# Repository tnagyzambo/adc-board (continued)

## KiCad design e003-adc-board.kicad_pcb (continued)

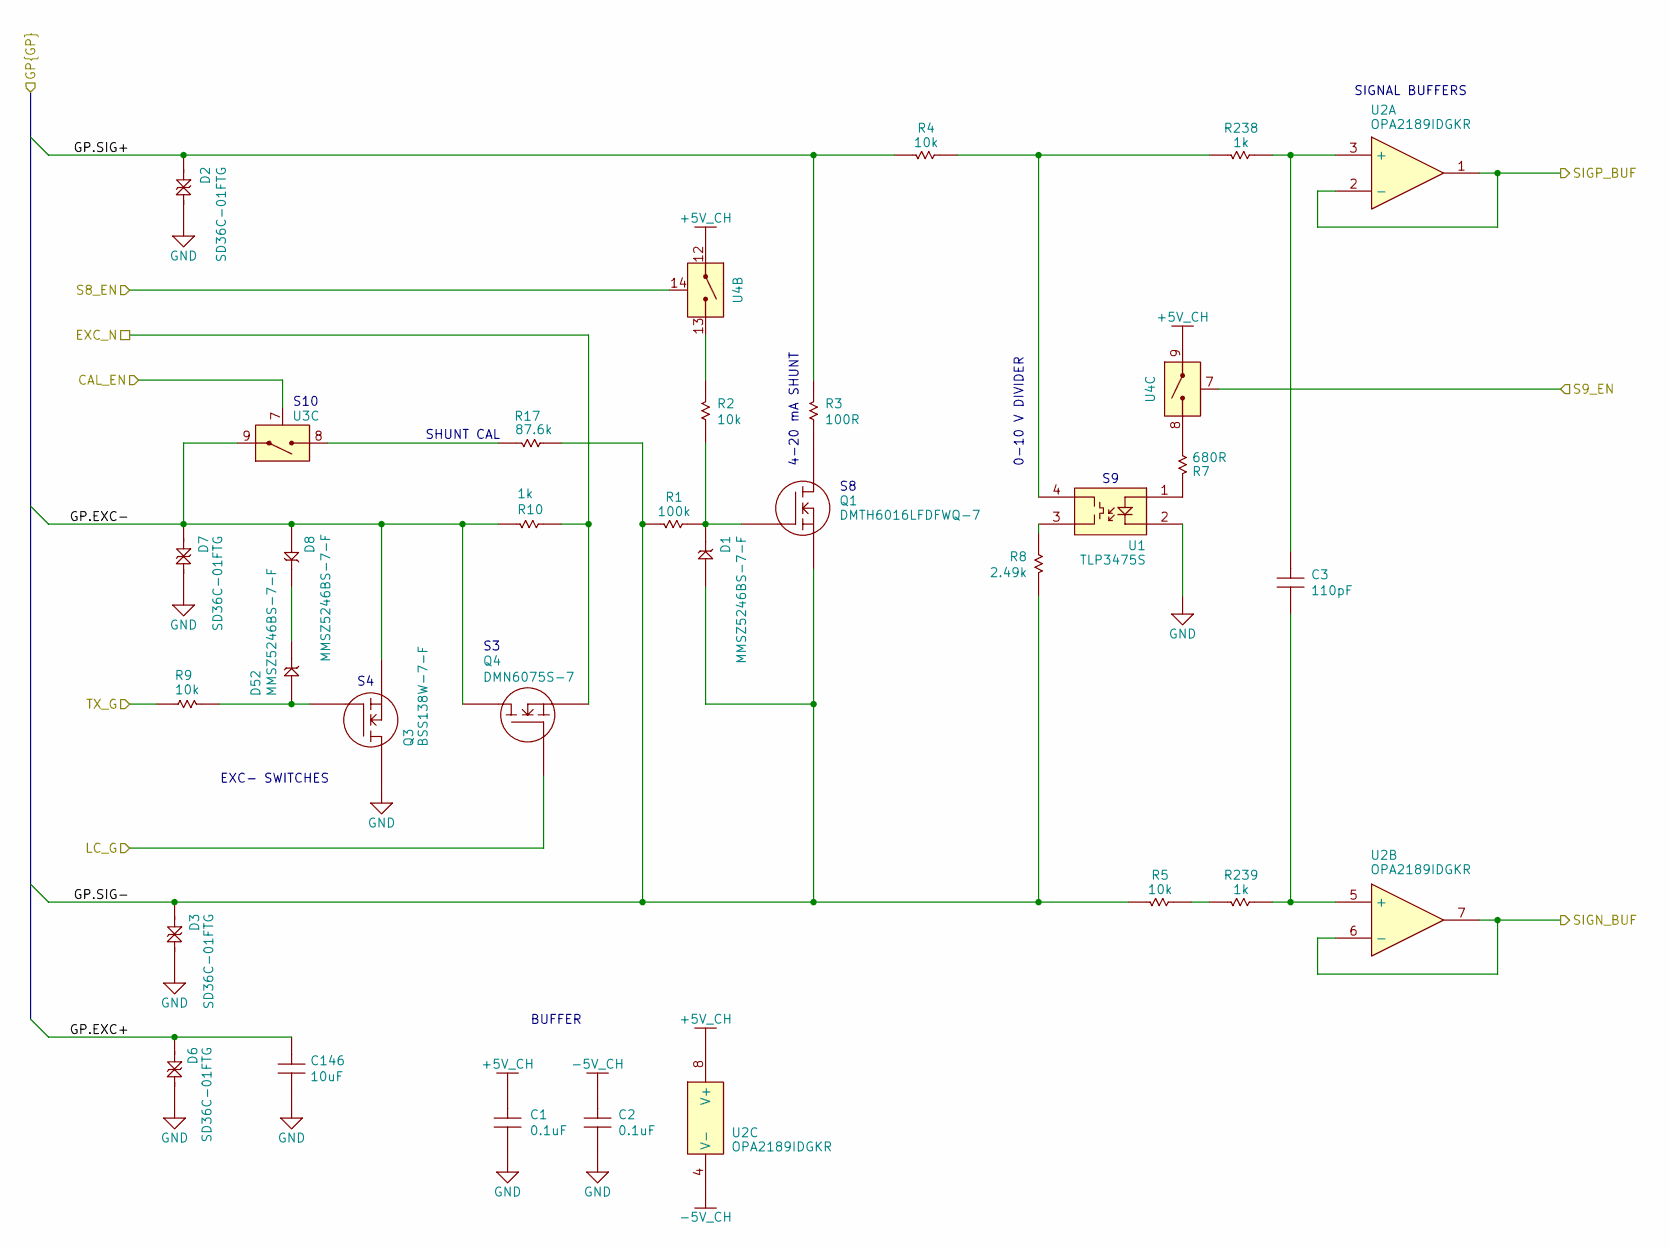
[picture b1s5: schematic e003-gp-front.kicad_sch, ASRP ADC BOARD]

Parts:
C1, C2: 0.1uF; MURATA-0402; Tolerance 10%; Voltage_Rating 50 VDC; MPN GRM155R71H104KE14J; DigiKey_Part 490-13342-2-ND
C3: 110pF; MURATA-0402; Tolerance 5%; Voltage_Rating 50 VDC; MPN GCM1555C1H111JA16D; DigiKey_Part 490-GCM1555C1H111JA16DCT-ND
C146: 10uF; MURATA-GRJ32-1210; Tolerance 10%; Voltage_Rating 50 VDC; MPN GRJ32ER71H106KE11; DigiKey_Part 490-10961-1-ND
D1, D8, D52: MMSZ5246BS-7-F; DIODES-SOD323; Voltage_Rating 16V; MPN MMSZ5246BS-7-F; DigiKey_Part MMSZ5246BS-FDICT-ND
D2, D3, D6, D7: SD36C-01FTG; LITTELFUSE-SOD323; Voltage_Rating 36V; MPN SD36C-01FTG; DigiKey_Part F6448CT-ND
Q1: DMTH6016LFDFWQ-7; DIODES-UDFN2020-6F; Voltage_Rating 60V; MPN DMTH6016LFDFWQ-7; DigiKey_Part DMTH6016LFDFWQ-7-ND
Q3: BSS138W-7-F; DIODES-SOT323; Voltage_Rating 50V; MPN BSS138W-7-F; DigiKey_Part BSS138W-FDICT-ND
Q4: DMN6075S-7; NEXPERIA-SOT23; Voltage_Rating 60V; MPN DMN6075S-7; DigiKey_Part DMN6075S-7DICT-ND
R1: 100k; VISHAY-0402; Tolerance 1%; MPN CRCW0402100KFKEDC; DigiKey_Part 541-3960-1-ND
R2, R9: 10k; VISHAY-0402; Tolerance 1%; MPN CRCW040210K0FKEDC; DigiKey_Part 541-3959-1-ND
R3: 100R; VISHAY-1206; Tolerance ±0.1%; MPN PHP01206E1000BST5; DigiKey_Part PHP100ACT-ND
R4: 10k; VISHAY-CRCW0805; Tolerance 0.05%; MPN TNPU080510K0AZEN00; DigiKey_Part TNPU10.0KABCT-ND
R5: 10k; VISHAY-CRCW0805; Tolerance 1%; MPN CRCW080510K0FKEA; DigiKey_Part 541-10.0KCCT-ND
R7: 680R; VISHAY-0402; Tolerance 1%; MPN CRCW0402680RFKED; DigiKey_Part 541-680LCT-ND
R8: 2.49k; VISHAY-1206; Tolerance 0.05%; MPN TNPU12062K49AZEN00; DigiKey_Part TNPU12062K49AZEN00-ND
R10: 1k; VISHAY-1206; Tolerance ±0.1%; MPN PHP01206E1001BST5; DigiKey_Part PHP1.00KACT-ND
R17: 87.6k; VISHAY-CRCW0805; Tolerance 0.1%; MPN TNPU080587K6BZEN00; DigiKey_Part none
R238, R239: 1k; VISHAY-0402; Tolerance 1%; MPN CRCW04021K00FKED; DigiKey_Part 541-1.00KLCT-ND
U1: TLP3475S; TOSHIBA-S-VSON4T; MPN TLP3475S; DigiKey_Part TLP3475S(TPECT-ND
U2: OPA2189IDGKR; TI-VSSOP-DGK0008A; MPN OPA2189IDGKR; DigiKey_Part 296-OPA2189IDGKRCT-ND
U3, U4: TMUX6212RUMR; TI-WQFN-RUM0016E; MPN TMUX6212RUMR; DigiKey_Part 296-TMUX6212RUMRCT-ND

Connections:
+5V_CH: C1.2, U2.8 (V+), U4.9 (S3), U4.12 (S2); also elsewhere on the board
-5V_CH: C2.2, U2.4 (V-); also elsewhere on the board
/GP1.EXC+: C146.2, D6.1 (A1); also elsewhere on the board
/GP1.EXC-: D7.1 (A1), D8.1 (0), Q3.2, Q4.3, R10.2, U3.9 (S3); also elsewhere on the board
/GP1.SIG+: D2.1 (A1), R3.2, R4.2; also elsewhere on the board
/GP1.SIG-: D1.1 (0), D3.1 (A1), Q1.2, R1.2, R5.2, R8.1, R17.2; also elsewhere on the board
/gp-ch1/converter/CAL_EN: U3.7 (SEL3); also elsewhere on the board
/gp-ch1/converter/EXC_N: Q4.2, R10.1; also elsewhere on the board
/gp-ch1/converter/LC_G: Q4.1; also elsewhere on the board
/gp-ch1/converter/S8_EN: U4.14 (SEL2); also elsewhere on the board
/gp-ch1/converter/S9_EN: U4.7 (SEL3); also elsewhere on the board
/gp-ch1/converter/SIGN_BUF: U2.6 (-), U2.7; also elsewhere on the board
/gp-ch1/converter/SIGP_BUF: U2.1, U2.2 (-); also elsewhere on the board
/gp-ch1/excitation/TX_G: R9.2; also elsewhere on the board
GND: C1.1, C2.1, C146.1, D2.2 (A2), D3.2 (A2), D6.2 (A2), D7.2 (A2), Q3.3, U1.2 (K); also elsewhere on the board
unnamed: D1.2 (1), Q1.1, R1.1, R2.1
unnamed: D52.1 (0), Q3.1, R9.1
unnamed: D8.2 (1), D52.2 (1)
unnamed: Q1.3, R3.1
unnamed: R8.2, U1.3 (D)
unnamed: R4.1, R238.2, U1.4 (D)
unnamed: R5.1, R239.2
unnamed: R7.1, U1.1 (A)
unnamed: C3.2, R238.1, U2.3 (+)
unnamed: C3.1, R239.1, U2.5 (+)
unnamed: R17.1, U3.8 (D3)
unnamed: R2.2, U4.13 (D2)
unnamed: R7.2, U4.8 (D3)

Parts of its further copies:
C59, C60: 0.1uF; MURATA-0402; Tolerance 10%; Voltage_Rating 50 VDC; MPN GRM155R71H104KE14J; DigiKey_Part 490-13342-2-ND
C61: 110pF; MURATA-0402; Tolerance 5%; Voltage_Rating 50 VDC; MPN GCM1555C1H111JA16D; DigiKey_Part 490-GCM1555C1H111JA16DCT-ND
C147: 10uF; MURATA-GRJ32-1210; Tolerance 10%; Voltage_Rating 50 VDC; MPN GRJ32ER71H106KE11; DigiKey_Part 490-10961-1-ND
D16, D23, D53: MMSZ5246BS-7-F; DIODES-SOD323; Voltage_Rating 16V; MPN MMSZ5246BS-7-F; DigiKey_Part MMSZ5246BS-FDICT-ND
D17, D18, D21, D22: SD36C-01FTG; LITTELFUSE-SOD323; Voltage_Rating 36V; MPN SD36C-01FTG; DigiKey_Part F6448CT-ND
Q11: DMTH6016LFDFWQ-7; DIODES-UDFN2020-6F; Voltage_Rating 60V; MPN DMTH6016LFDFWQ-7; DigiKey_Part DMTH6016LFDFWQ-7-ND
Q13: BSS138W-7-F; DIODES-SOT323; Voltage_Rating 50V; MPN BSS138W-7-F; DigiKey_Part BSS138W-FDICT-ND
Q14: DMN6075S-7; NEXPERIA-SOT23; Voltage_Rating 60V; MPN DMN6075S-7; DigiKey_Part DMN6075S-7DICT-ND
R72: 100k; VISHAY-0402; Tolerance 1%; MPN CRCW0402100KFKEDC; DigiKey_Part 541-3960-1-ND
R73, R80: 10k; VISHAY-0402; Tolerance 1%; MPN CRCW040210K0FKEDC; DigiKey_Part 541-3959-1-ND
R74: 100R; VISHAY-1206; Tolerance ±0.1%; MPN PHP01206E1000BST5; DigiKey_Part PHP100ACT-ND
R75: 10k; VISHAY-CRCW0805; Tolerance 0.05%; MPN TNPU080510K0AZEN00; DigiKey_Part TNPU10.0KABCT-ND
R76: 10k; VISHAY-CRCW0805; Tolerance 1%; MPN CRCW080510K0FKEA; DigiKey_Part 541-10.0KCCT-ND
R78: 680R; VISHAY-0402; Tolerance 1%; MPN CRCW0402680RFKED; DigiKey_Part 541-680LCT-ND
R79: 2.49k; VISHAY-1206; Tolerance 0.05%; MPN TNPU12062K49AZEN00; DigiKey_Part TNPU12062K49AZEN00-ND
R81: 1k; VISHAY-1206; Tolerance ±0.1%; MPN PHP01206E1001BST5; DigiKey_Part PHP1.00KACT-ND
R108: 87.6k; VISHAY-CRCW0805; Tolerance 0.1%; MPN TNPU080587K6BZEN00; DigiKey_Part none
R240, R241: 1k; VISHAY-0402; Tolerance 1%; MPN CRCW04021K00FKED; DigiKey_Part 541-1.00KLCT-ND
U15, U29: TMUX6212RUMR; TI-WQFN-RUM0016E; MPN TMUX6212RUMR; DigiKey_Part 296-TMUX6212RUMRCT-ND
U23: TLP3475S; TOSHIBA-S-VSON4T; MPN TLP3475S; DigiKey_Part TLP3475S(TPECT-ND
U24: OPA2189IDGKR; TI-VSSOP-DGK0008A; MPN OPA2189IDGKR; DigiKey_Part 296-OPA2189IDGKRCT-ND

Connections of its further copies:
+5V_CH: C59.2, U15.1 (S1), U15.4 (S4), U15.9 (S3), U15.11 (VDD), U15.12 (S2), U24.8 (V+), U29.4 (S4), U29.11 (VDD); also elsewhere on the board
-5V_CH: C60.2, U15.2 (VSS), U24.4 (V-), U29.2 (VSS); also elsewhere on the board
/GP2.EXC+: C147.2, D21.1 (A1); also elsewhere on the board
/GP2.EXC-: D22.1 (A1), D23.1 (0), Q13.2, Q14.3, R81.2, U29.1 (S1), U29.9 (S3); also elsewhere on the board
/GP2.SIG+: D17.1 (A1), R74.2, R75.2; also elsewhere on the board
/GP2.SIG-: D16.1 (0), D18.1 (A1), Q11.2, R72.2, R76.2, R79.1, R108.2; also elsewhere on the board
/gp-ch2/converter/CAL_EN: U29.7 (SEL3); also elsewhere on the board
/gp-ch2/converter/EXC_N: Q14.2, R81.1; also elsewhere on the board
/gp-ch2/converter/EXC_P: U29.12 (S2); also elsewhere on the board
/gp-ch2/converter/LC_EN: U29.6 (SEL4); also elsewhere on the board
/gp-ch2/converter/LC_G: Q14.1, U29.5 (D4); also elsewhere on the board
/gp-ch2/converter/PRT_EN: U29.15 (SEL1); also elsewhere on the board
/gp-ch2/converter/S8_EN: U15.14 (SEL2); also elsewhere on the board
/gp-ch2/converter/S9_EN: U15.7 (SEL3); also elsewhere on the board
/gp-ch2/converter/SHLD_EN: U15.6 (SEL4); also elsewhere on the board
/gp-ch2/converter/SIGN_BUF: U24.6 (-), U24.7; also elsewhere on the board
/gp-ch2/converter/SIGP_BUF: U24.1, U24.2 (-); also elsewhere on the board
/gp-ch2/converter/TX_EN: U15.15 (SEL1), U29.14 (SEL2); also elsewhere on the board
/gp-ch2/excitation/TX_G: R80.2, U15.16 (D1); also elsewhere on the board
GND: C59.1, C60.1, C147.1, D17.2 (A2), D18.2 (A2), D21.2 (A2), D22.2 (A2), Q13.3, U15.3 (GND), U23.2 (K), U29.3 (GND); also elsewhere on the board
unnamed: D16.2 (1), Q11.1, R72.1, R73.1
unnamed: D23.2 (1), D53.2 (1)
unnamed: D53.1 (0), Q13.1, R80.1
unnamed: Q11.3, R74.1
unnamed: R79.2, U23.3 (D)
unnamed: R75.1, R240.2, U23.4 (D)
unnamed: R76.1, R241.2
unnamed: R73.2, U15.13 (D2)
unnamed: R78.2, U15.8 (D3)
unnamed 168: U15.5 (D4); also elsewhere on the board
unnamed: R78.1, U23.1 (A)
unnamed: C61.2, R240.1, U24.3 (+)
unnamed: C61.1, R241.1, U24.5 (+)
unnamed 176: U29.13 (D2), U29.16 (D1); also elsewhere on the board
unnamed: R108.1, U29.8 (D3)

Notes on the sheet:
SHUNT CAL
BUFFER
0-10 V DIVIDER
EXC- SWITCHES
S10
4-20 mA SHUNT
SIGNAL BUFFERS

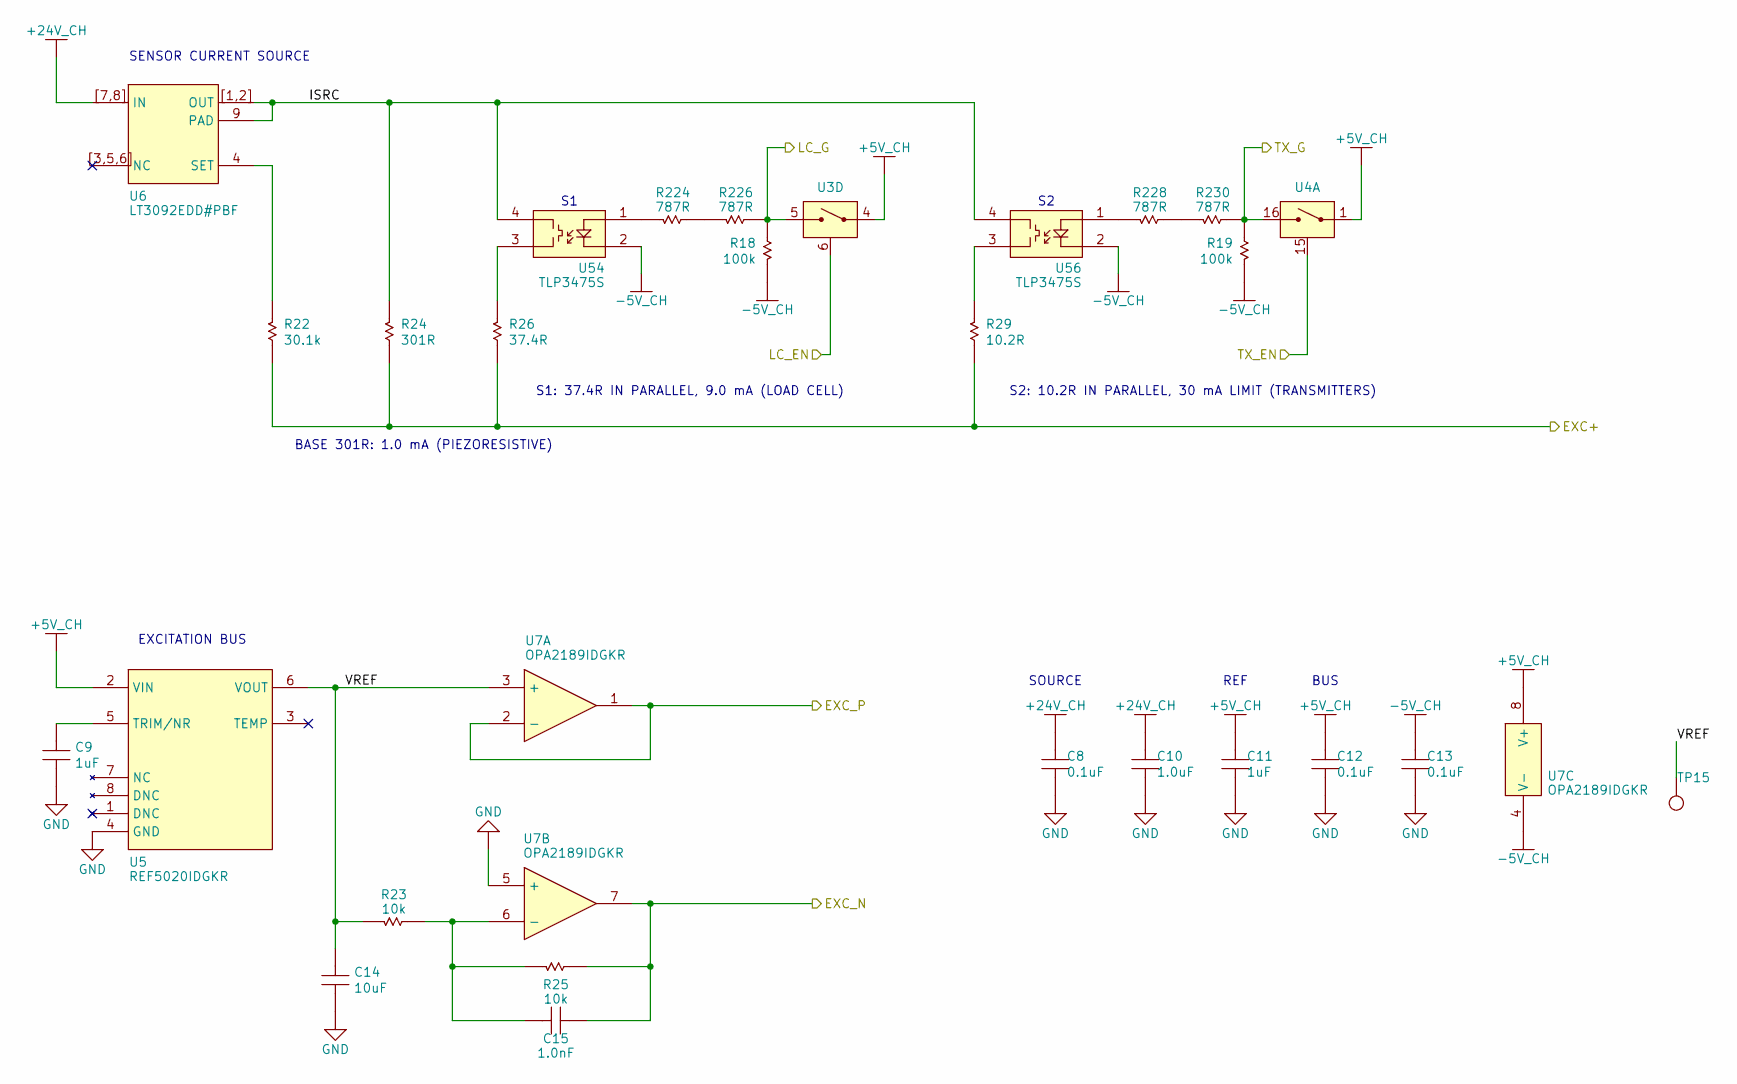
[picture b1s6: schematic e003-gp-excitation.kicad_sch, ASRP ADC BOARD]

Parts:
C8, C12, C13: 0.1uF; MURATA-0402; Tolerance 10%; Voltage_Rating 50 VDC; MPN GRM155R71H104KE14J; DigiKey_Part 490-13342-2-ND
C9, C11: 1uF; MURATA-0402; Tolerance 10%; Voltage_Rating 10 VDC; MPN GRM155Z71A105KE01D; DigiKey_Part 490-GRM155Z71A105KE01DCT-ND
C10: 1.0uF; MURATA-0805; Tolerance 10%; Voltage_Rating 50 VDC; MPN GCJ21BR71H105KA01L; DigiKey_Part 490-10667-1-ND
C14: 10uF; MURATA-0805; Tolerance 10%; Voltage_Rating 25 VDC; MPN GRM21BZ71E106KE15K; DigiKey_Part 490-GRM21BZ71E106KE15KCT-ND
C15: 1.0nF; MURATA-0402; Tolerance 5%; Voltage_Rating 50 VDC; MPN GRM1555C1H102JA01D; DigiKey_Part 490-3244-1-ND
R18, R19: 100k; VISHAY-0402; Tolerance 1%; MPN CRCW0402100KFKEDC; DigiKey_Part 541-3960-1-ND
R22: 30.1k; VISHAY-0402; Tolerance 1%; MPN CRCW040230K1FKED; DigiKey_Part 541-30.1KLCT-ND
R23, R25: 10k; VISHAY-CRCW0805; Tolerance 0.05%; MPN TNPU080510K0AZEN00; DigiKey_Part TNPU10.0KABCT-ND
R24: 301R; VISHAY-0402; Tolerance 1%; MPN CRCW0402301RFKED; DigiKey_Part 541-301LCT-ND
R26: 37.4R; VISHAY-0402; Tolerance 1%; MPN CRCW040237R4FKED; DigiKey_Part 541-37.4LCT-ND
R29: 10.2R; VISHAY-0402; Tolerance 1%; MPN CRCW040210R2FKED; DigiKey_Part 541-10.2LCT-ND
R224, R226, R228, R230: 787R; VISHAY-0402; Tolerance 1%; MPN CRCW0402787RFKEDC; DigiKey_Part 541-5082-2-ND
TP15: PCB-TEST-POINT; PCB-PROBEPOINT; MPN N/A
U3, U4: TMUX6212RUMR; TI-WQFN-RUM0016E; MPN TMUX6212RUMR; DigiKey_Part 296-TMUX6212RUMRCT-ND
U5: REF5020IDGKR; TI-VSSOP-DGK0008A; MPN REF5020IDGKR; DigiKey_Part 296-REF5020IDGKRCT-ND
U6: LT3092EDD#PBF; ADI-DFN-DD8; MPN LT3092EDD#PBF; DigiKey_Part 505-LT3092EDD#PBF-ND
U7: OPA2189IDGKR; TI-VSSOP-DGK0008A; MPN OPA2189IDGKR; DigiKey_Part 296-OPA2189IDGKRCT-ND
U54, U56: TLP3475S; TOSHIBA-S-VSON4T; MPN TLP3475S; DigiKey_Part TLP3475S(TPECT-ND

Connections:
+5V_CH: C11.2, C12.2, U3.4 (S4), U4.1 (S1), U5.2 (VIN), U7.8 (V+); also elsewhere on the board
+24V_CH: C8.2, C10.2, U6.7 (IN), U6.8 (IN), U6.[7,8] (IN); also elsewhere on the board
-5V_CH: C13.2, R18.1, R19.1, U7.4 (V-), U54.2 (K), U56.2 (K); also elsewhere on the board
/GP1.EXC+: R22.1, R24.1, R26.1, R29.1; also elsewhere on the board
/gp-ch1/converter/EXC_N: C15.1, R25.1, U7.7; also elsewhere on the board
/gp-ch1/converter/EXC_P: U7.1, U7.2 (-); also elsewhere on the board
/gp-ch1/converter/LC_EN: U3.6 (SEL4); also elsewhere on the board
/gp-ch1/converter/LC_G: R18.2, R226.1, U3.5 (D4); also elsewhere on the board
/gp-ch1/converter/TX_EN: U4.15 (SEL1); also elsewhere on the board
/gp-ch1/excitation/ISRC: R24.2, U6.1 (OUT), U6.2 (OUT), U6.9 (PAD), U6.[1,2] (OUT), U54.4 (D), U56.4 (D)
/gp-ch1/excitation/TX_G: R19.2, R230.1, U4.16 (D1); also elsewhere on the board
/gp-ch1/excitation/VREF: C14.2, R23.2, TP15.1 (0_1), U5.6 (VOUT), U7.3 (+)
GND: C8.1, C9.1, C10.1, C11.1, C12.1, C13.1, C14.1, U5.4 (GND), U7.5 (+); also elsewhere on the board
unnamed: R26.2, U54.3 (D)
unnamed: R29.2, U56.3 (D)
unnamed: R224.1, R226.2
unnamed: R228.1, R230.2
unnamed: C9.2, U5.5 (TRIM/NR)
unnamed: R22.2, U6.4 (SET)
unnamed: C15.2, R23.1, R25.2, U7.6 (-)
unnamed: R224.2, U54.1 (A)
unnamed: R228.2, U56.1 (A)

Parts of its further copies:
C80, C84, C85: 0.1uF; MURATA-0402; Tolerance 10%; Voltage_Rating 50 VDC; MPN GRM155R71H104KE14J; DigiKey_Part 490-13342-2-ND
C82: 1.0uF; MURATA-0805; Tolerance 10%; Voltage_Rating 50 VDC; MPN GCJ21BR71H105KA01L; DigiKey_Part 490-10667-1-ND
C87: 1.0nF; MURATA-0402; Tolerance 5%; Voltage_Rating 50 VDC; MPN GRM1555C1H102JA01D; DigiKey_Part 490-3244-1-ND
C166: 10uF; MURATA-0805; Tolerance 10%; Voltage_Rating 25 VDC; MPN GRM21BZ71E106KE15K; DigiKey_Part 490-GRM21BZ71E106KE15KCT-ND
C167, C168: 1uF; MURATA-0402; Tolerance 10%; Voltage_Rating 10 VDC; MPN GRM155Z71A105KE01D; DigiKey_Part 490-GRM155Z71A105KE01DCT-ND
R27, R28: 100k; VISHAY-0402; Tolerance 1%; MPN CRCW0402100KFKEDC; DigiKey_Part 541-3960-1-ND
R135: 30.1k; VISHAY-0402; Tolerance 1%; MPN CRCW040230K1FKED; DigiKey_Part 541-30.1KLCT-ND
R136, R138: 10k; VISHAY-CRCW0805; Tolerance 0.05%; MPN TNPU080510K0AZEN00; DigiKey_Part TNPU10.0KABCT-ND
R137: 301R; VISHAY-0402; Tolerance 1%; MPN CRCW0402301RFKED; DigiKey_Part 541-301LCT-ND
R139: 37.4R; VISHAY-0402; Tolerance 1%; MPN CRCW040237R4FKED; DigiKey_Part 541-37.4LCT-ND
R142: 10.2R; VISHAY-0402; Tolerance 1%; MPN CRCW040210R2FKED; DigiKey_Part 541-10.2LCT-ND
R225, R227, R229, R231: 787R; VISHAY-0402; Tolerance 1%; MPN CRCW0402787RFKEDC; DigiKey_Part 541-5082-2-ND
TP16: PCB-TEST-POINT; PCB-PROBEPOINT; MPN N/A
U15, U29: TMUX6212RUMR; TI-WQFN-RUM0016E; MPN TMUX6212RUMR; DigiKey_Part 296-TMUX6212RUMRCT-ND
U36: LT3092EDD#PBF; ADI-DFN-DD8; MPN LT3092EDD#PBF; DigiKey_Part 505-LT3092EDD#PBF-ND
U37: OPA2189IDGKR; TI-VSSOP-DGK0008A; MPN OPA2189IDGKR; DigiKey_Part 296-OPA2189IDGKRCT-ND
U53: REF5020IDGKR; TI-VSSOP-DGK0008A; MPN REF5020IDGKR; DigiKey_Part 296-REF5020IDGKRCT-ND
U55, U57: TLP3475S; TOSHIBA-S-VSON4T; MPN TLP3475S; DigiKey_Part TLP3475S(TPECT-ND

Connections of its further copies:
+5V_CH: C84.2, C167.2, U15.1 (S1), U15.4 (S4), U15.9 (S3), U15.11 (VDD), U15.12 (S2), U29.4 (S4), U29.11 (VDD), U37.8 (V+), U53.2 (VIN); also elsewhere on the board
+24V_CH: C80.2, C82.2, U36.7 (IN), U36.8 (IN); also elsewhere on the board
-5V_CH: C85.2, R27.1, R28.1, U15.2 (VSS), U29.2 (VSS), U37.4 (V-), U55.2 (K), U57.2 (K); also elsewhere on the board
/GP2.EXC+: R135.1, R137.1, R139.1, R142.1; also elsewhere on the board
/GP2.EXC-: U29.1 (S1), U29.9 (S3); also elsewhere on the board
/gp-ch2/converter/CAL_EN: U29.7 (SEL3); also elsewhere on the board
/gp-ch2/converter/EXC_N: C87.1, R138.1, U37.7; also elsewhere on the board
/gp-ch2/converter/EXC_P: U29.12 (S2), U37.1, U37.2 (-); also elsewhere on the board
/gp-ch2/converter/LC_EN: U29.6 (SEL4); also elsewhere on the board
/gp-ch2/converter/LC_G: R27.2, R227.1, U29.5 (D4); also elsewhere on the board
/gp-ch2/converter/PRT_EN: U29.15 (SEL1); also elsewhere on the board
/gp-ch2/converter/S8_EN: U15.14 (SEL2); also elsewhere on the board
/gp-ch2/converter/S9_EN: U15.7 (SEL3); also elsewhere on the board
/gp-ch2/converter/SHLD_EN: U15.6 (SEL4); also elsewhere on the board
/gp-ch2/converter/TX_EN: U15.15 (SEL1), U29.14 (SEL2); also elsewhere on the board
/gp-ch2/excitation/ISRC: R137.2, U36.1 (OUT), U36.2 (OUT), U36.9 (PAD), U55.4 (D), U57.4 (D)
/gp-ch2/excitation/TX_G: R28.2, R231.1, U15.16 (D1); also elsewhere on the board
/gp-ch2/excitation/VREF: C166.2, R136.2, TP16.1 (0_1), U37.3 (+), U53.6 (VOUT)
GND: C80.1, C82.1, C84.1, C85.1, C166.1, C167.1, C168.1, U15.3 (GND), U29.3 (GND), U37.5 (+), U53.4 (GND); also elsewhere on the board
unnamed: R139.2, U55.3 (D)
unnamed: R142.2, U57.3 (D)
unnamed: R225.1, R227.2
unnamed: R229.1, R231.2
unnamed 166: U15.13 (D2); also elsewhere on the board
unnamed 167: U15.8 (D3); also elsewhere on the board
unnamed 168: U15.5 (D4); also elsewhere on the board
unnamed 176: U29.13 (D2), U29.16 (D1); also elsewhere on the board
unnamed 177: U29.8 (D3); also elsewhere on the board
unnamed: R135.2, U36.4 (SET)
unnamed: C87.2, R136.1, R138.2, U37.6 (-)
unnamed: C168.2, U53.5 (TRIM/NR)
unnamed: R225.2, U55.1 (A)
unnamed: R229.2, U57.1 (A)

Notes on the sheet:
S1: 37.4R IN PARALLEL, 9.0 mA (LOAD CELL)
SOURCE
REF
BASE 301R: 1.0 mA (PIEZORESISTIVE)
SENSOR CURRENT SOURCE
S2: 10.2R IN PARALLEL, 30 mA LIMIT (TRANSMITTERS)
BUS
EXCITATION BUS

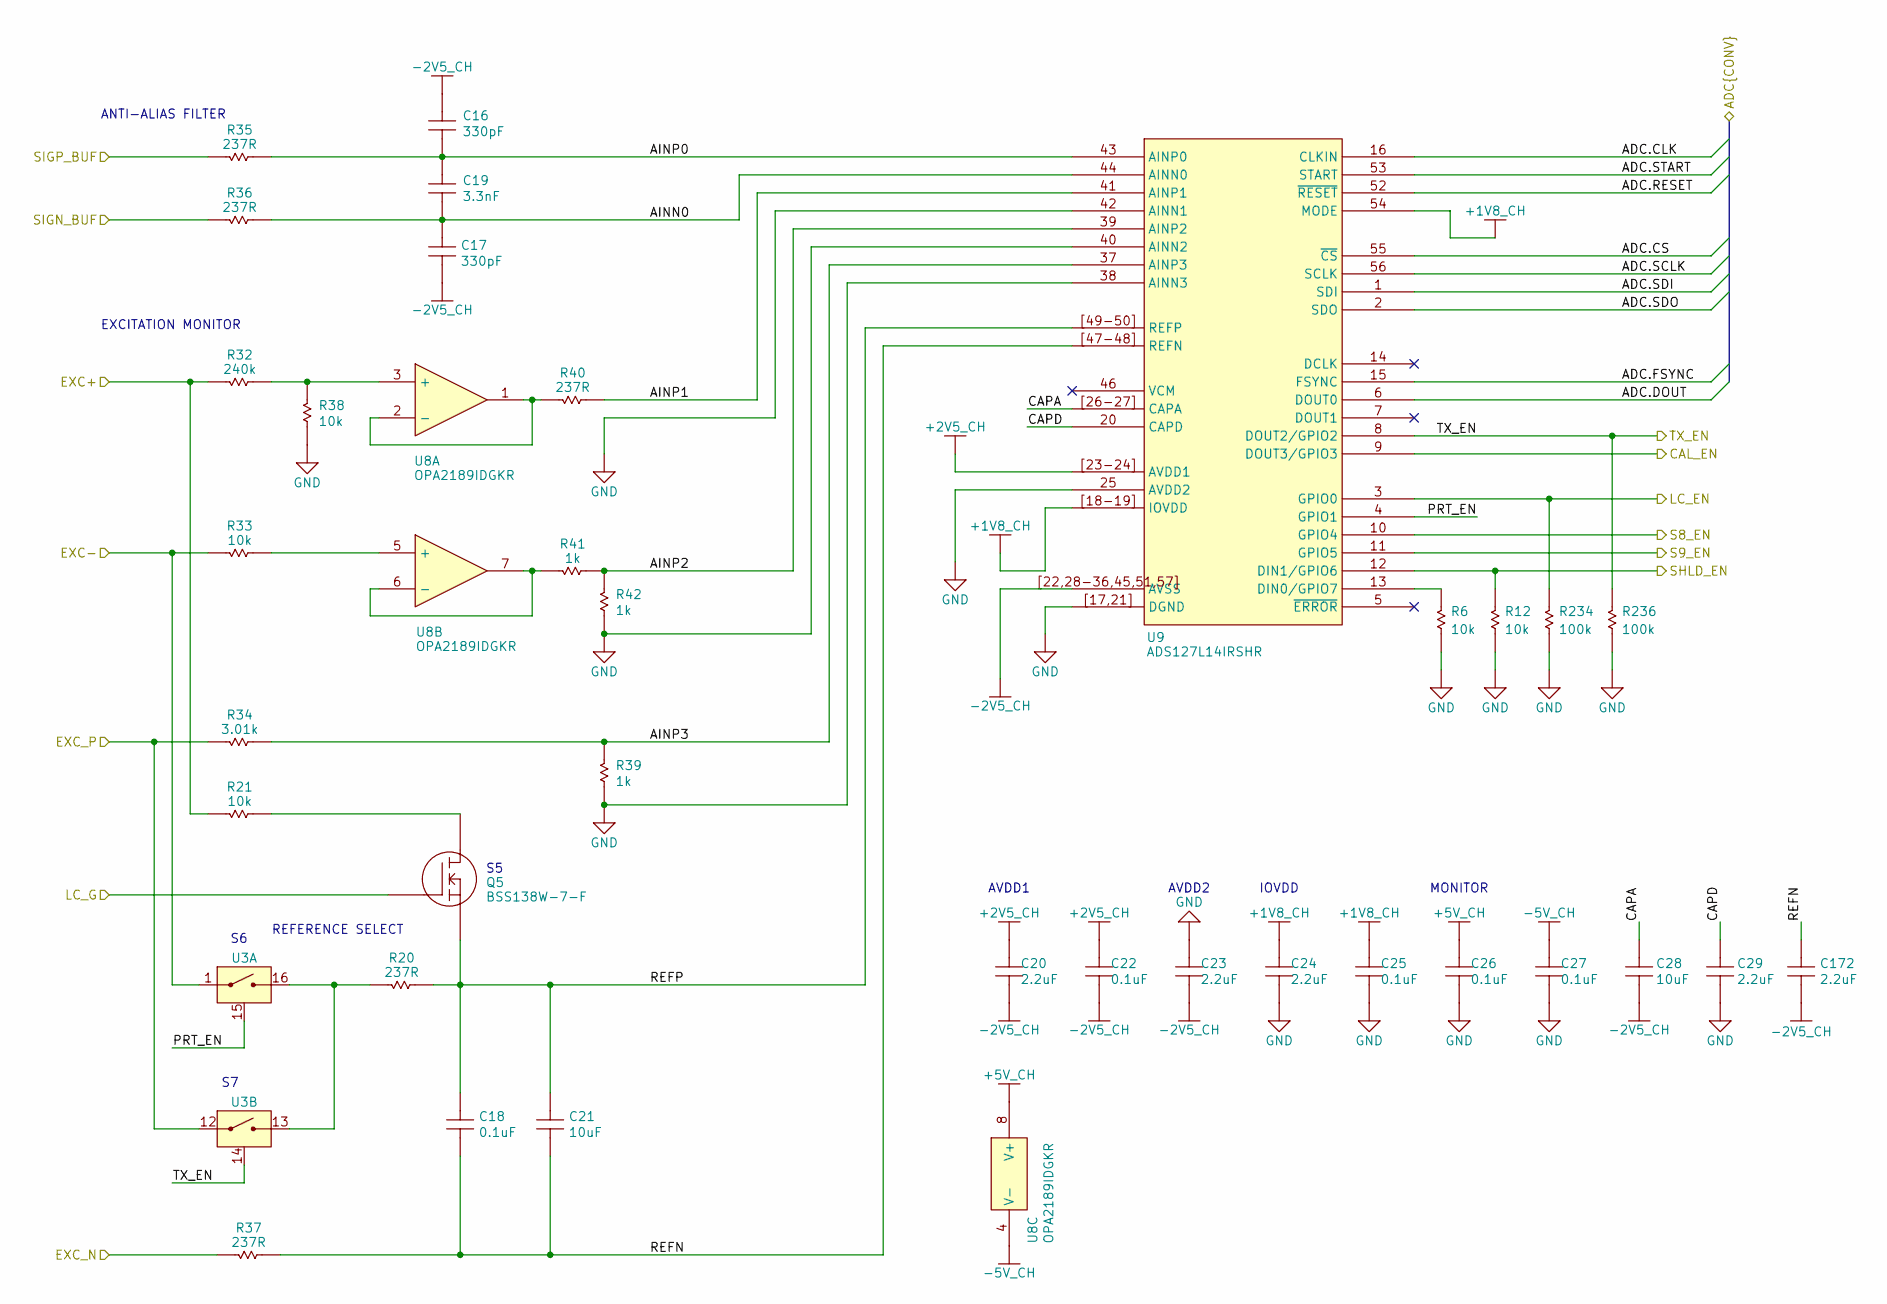
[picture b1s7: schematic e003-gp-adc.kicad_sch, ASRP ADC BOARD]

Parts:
C16, C17: 330pF; MURATA-0402; Tolerance 5%; Voltage_Rating 50 VDC; MPN GRM1555C1H331JA01D; DigiKey_Part 490-1295-1-ND
C18, C22, C25, C26, C27: 0.1uF; MURATA-0402; Tolerance 10%; Voltage_Rating 50 VDC; MPN GRM155R71H104KE14J; DigiKey_Part 490-13342-2-ND
C19: 3.3nF; MURATA-0402; Tolerance 5%; Voltage_Rating 50 VDC; MPN GRM1555C1H332JE01J; DigiKey_Part 490-GRM1555C1H332JE01JCT-ND
C20, C23, C24, C29, C172: 2.2uF; MURATA-0402; Tolerance 10%; Voltage_Rating 10 VDC; MPN GRM155Z71A225KE01J; DigiKey_Part 490-GRM155Z71A225KE01JCT-ND
C21, C28: 10uF; MURATA-0805; Tolerance 10%; Voltage_Rating 25 VDC; MPN GRM21BZ71E106KE15K; DigiKey_Part 490-GRM21BZ71E106KE15KCT-ND
Q5: BSS138W-7-F; DIODES-SOT323; Voltage_Rating 50V; MPN BSS138W-7-F; DigiKey_Part BSS138W-FDICT-ND
R6, R12, R21, R33: 10k; VISHAY-0402; Tolerance 1%; MPN CRCW040210K0FKEDC; DigiKey_Part 541-3959-1-ND
R20, R35, R36, R37, R40: 237R; VISHAY-0402; Tolerance 0.1%; MPN TNPW0402237RBEED; DigiKey_Part TNPW0402237RBEED-ND
R32: 240k; VISHAY-CRCW0805; Tolerance 0.1%; MPN TNPU0805240KBZEN00; DigiKey_Part TNPU0805240KBZEN00-ND
R34: 3.01k; VISHAY-0402; Tolerance 0.1%; MPN TNPU04023K01BZEP00; DigiKey_Part 541-TNPU04023K01BZEP00CT-ND
R38: 10k; VISHAY-0402; Tolerance 0.1%; MPN TNPU040210K0BZEP00; DigiKey_Part 541-TNPU040210K0BZEP00CT-ND
R39, R41, R42: 1k; VISHAY-0402; Tolerance 0.1%; MPN TNPU04021K00BZEP00; DigiKey_Part 541-TNPU04021K00BZEP00CT-ND
R234, R236: 100k; VISHAY-0402; Tolerance 1%; MPN CRCW0402100KFKEDC; DigiKey_Part 541-3960-1-ND
U3: TMUX6212RUMR; TI-WQFN-RUM0016E; MPN TMUX6212RUMR; DigiKey_Part 296-TMUX6212RUMRCT-ND
U8: OPA2189IDGKR; TI-VSSOP-DGK0008A; MPN OPA2189IDGKR; DigiKey_Part 296-OPA2189IDGKRCT-ND
U9: ADS127L14IRSHR; TI-VQFN-RSH0056G; MPN ADS127L14IRSHR; DigiKey_Part 296-ADS127L14IRSHRTR-ND

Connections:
+1V8_CH: C24.2, C25.2, U9.18 (IOVDD), U9.19 (IOVDD), U9.54 (MODE), U9.[18-19] (IOVDD); also elsewhere on the board
+2V5_CH: C20.2, C22.2, U9.23 (AVDD1), U9.24 (AVDD1), U9.[23-24] (AVDD1); also elsewhere on the board
+5V_CH: C26.2, U8.8 (V+); also elsewhere on the board
-2V5_CH: C16.2, C17.1, C20.1, C22.1, C23.1, C28.1, C172.1, U9.22 (AVSS), U9.28 (AVSS), U9.29 (AVSS), U9.30 (AVSS), U9.31 (AVSS), U9.32 (AVSS), U9.33 (AVSS), U9.34 (AVSS), U9.35 (AVSS), U9.36 (AVSS), U9.45 (AVSS), U9.51 (AVSS), U9.57 (AVSS), U9.[22,28-36,45,51,57] (AVSS); also elsewhere on the board
-5V_CH: C27.2, U8.4 (V-); also elsewhere on the board
/GP1.EXC+: R21.2, R32.2; also elsewhere on the board
/GP1.EXC-: R33.2, U3.1 (S1); also elsewhere on the board
/fpga/ADC1.CLK: U9.16 (CLKIN); also elsewhere on the board
/fpga/ADC1.CS: U9.55 (~CS); also elsewhere on the board
/fpga/ADC1.DOUT: U9.6 (DOUT0); also elsewhere on the board
/fpga/ADC1.FSYNC: U9.15 (FSYNC); also elsewhere on the board
/fpga/ADC1.RESET: U9.52 (~RESET); also elsewhere on the board
/fpga/ADC1.SCLK: U9.56 (SCLK); also elsewhere on the board
/fpga/ADC1.SDI: U9.1 (SDI); also elsewhere on the board
/fpga/ADC1.SDO: U9.2 (SDO); also elsewhere on the board
/fpga/ADC1.START: U9.53 (START); also elsewhere on the board
/gp-ch1/converter/AINN0: C17.2, C19.1, R36.1, U9.44 (AINN0)
/gp-ch1/converter/AINP0: C16.1, C19.2, R35.1, U9.43 (AINP0)
/gp-ch1/converter/AINP1: R40.1, U9.41 (AINP1)
/gp-ch1/converter/AINP2: R41.1, R42.2, U9.39 (AINP2)
/gp-ch1/converter/AINP3: R34.1, R39.2, U9.37 (AINP3)
/gp-ch1/converter/CAL_EN: U9.9 (DOUT3/GPIO3); also elsewhere on the board
/gp-ch1/converter/CAPA: C28.2, U9.26 (CAPA), U9.27 (CAPA), U9.[26-27] (CAPA)
/gp-ch1/converter/CAPD: C29.2, U9.20 (CAPD)
/gp-ch1/converter/EXC_N: R37.2; also elsewhere on the board
/gp-ch1/converter/EXC_P: R34.2, U3.12 (S2); also elsewhere on the board
/gp-ch1/converter/LC_EN: R234.2, U9.3 (GPIO0); also elsewhere on the board
/gp-ch1/converter/LC_G: Q5.1; also elsewhere on the board
/gp-ch1/converter/PRT_EN: U3.15 (SEL1), U9.4 (GPIO1)
/gp-ch1/converter/REFN: C18.1, C21.1, C172.2, R37.1, U9.47 (REFN), U9.48 (REFN), U9.[47-48] (REFN)
/gp-ch1/converter/REFP: C18.2, C21.2, Q5.2, R20.1, U9.49 (REFP), U9.50 (REFP), U9.[49-50] (REFP)
/gp-ch1/converter/S8_EN: U9.10 (GPIO4); also elsewhere on the board
/gp-ch1/converter/S9_EN: U9.11 (GPIO5); also elsewhere on the board
/gp-ch1/converter/SHLD_EN: R12.2, U9.12 (DIN1/GPIO6); also elsewhere on the board
/gp-ch1/converter/SIGN_BUF: R36.2; also elsewhere on the board
/gp-ch1/converter/SIGP_BUF: R35.2; also elsewhere on the board
/gp-ch1/converter/TX_EN: R236.2, U3.14 (SEL2), U9.8 (DOUT2/GPIO2); also elsewhere on the board
GND: C23.2, C24.1, C25.1, C26.1, C27.1, C29.1, R6.1, R12.1, R38.1, R39.1, R42.1, R234.1, R236.1, U9.17 (DGND), U9.21 (DGND), U9.25 (AVDD2), U9.38 (AINN3), U9.40 (AINN2), U9.42 (AINN1), U9.[17,21] (DGND); also elsewhere on the board
unnamed: Q5.3, R21.1
unnamed: R20.2, U3.13 (D2), U3.16 (D1)
unnamed: R32.1, R38.2, U8.3 (+)
unnamed: R40.2, U8.1, U8.2 (-)
unnamed: R33.1, U8.5 (+)
unnamed: R41.2, U8.6 (-), U8.7
unnamed: R6.2, U9.13 (DIN0/GPIO7)

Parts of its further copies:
C104, C105: 330pF; MURATA-0402; Tolerance 5%; Voltage_Rating 50 VDC; MPN GRM1555C1H331JA01D; DigiKey_Part 490-1295-1-ND
C106, C110, C113, C114, C115: 0.1uF; MURATA-0402; Tolerance 10%; Voltage_Rating 50 VDC; MPN GRM155R71H104KE14J; DigiKey_Part 490-13342-2-ND
C107: 3.3nF; MURATA-0402; Tolerance 5%; Voltage_Rating 50 VDC; MPN GRM1555C1H332JE01J; DigiKey_Part 490-GRM1555C1H332JE01JCT-ND
C108, C111, C112, C117, C173: 2.2uF; MURATA-0402; Tolerance 10%; Voltage_Rating 10 VDC; MPN GRM155Z71A225KE01J; DigiKey_Part 490-GRM155Z71A225KE01JCT-ND
C109, C116: 10uF; MURATA-0805; Tolerance 10%; Voltage_Rating 25 VDC; MPN GRM21BZ71E106KE15K; DigiKey_Part 490-GRM21BZ71E106KE15KCT-ND
Q23: BSS138W-7-F; DIODES-SOT323; Voltage_Rating 50V; MPN BSS138W-7-F; DigiKey_Part BSS138W-FDICT-ND
R11, R13, R112, R166: 10k; VISHAY-0402; Tolerance 1%; MPN CRCW040210K0FKEDC; DigiKey_Part 541-3959-1-ND
R111, R168, R169, R170, R173: 237R; VISHAY-0402; Tolerance 0.1%; MPN TNPW0402237RBEED; DigiKey_Part TNPW0402237RBEED-ND
R165: 240k; VISHAY-CRCW0805; Tolerance 0.1%; MPN TNPU0805240KBZEN00; DigiKey_Part TNPU0805240KBZEN00-ND
R167: 3.01k; VISHAY-0402; Tolerance 0.1%; MPN TNPU04023K01BZEP00; DigiKey_Part 541-TNPU04023K01BZEP00CT-ND
R171: 10k; VISHAY-0402; Tolerance 0.1%; MPN TNPU040210K0BZEP00; DigiKey_Part 541-TNPU040210K0BZEP00CT-ND
R172, R174, R175: 1k; VISHAY-0402; Tolerance 0.1%; MPN TNPU04021K00BZEP00; DigiKey_Part 541-TNPU04021K00BZEP00CT-ND
R235, R237: 100k; VISHAY-0402; Tolerance 1%; MPN CRCW0402100KFKEDC; DigiKey_Part 541-3960-1-ND
U29: TMUX6212RUMR; TI-WQFN-RUM0016E; MPN TMUX6212RUMR; DigiKey_Part 296-TMUX6212RUMRCT-ND
U44: OPA2189IDGKR; TI-VSSOP-DGK0008A; MPN OPA2189IDGKR; DigiKey_Part 296-OPA2189IDGKRCT-ND
U45: ADS127L14IRSHR; TI-VQFN-RSH0056G; MPN ADS127L14IRSHR; DigiKey_Part 296-ADS127L14IRSHRTR-ND

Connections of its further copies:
+1V8_CH: C112.2, C113.2, U45.18 (IOVDD), U45.19 (IOVDD), U45.54 (MODE); also elsewhere on the board
+2V5_CH: C108.2, C110.2, U45.23 (AVDD1), U45.24 (AVDD1); also elsewhere on the board
+5V_CH: C114.2, U29.4 (S4), U29.11 (VDD), U44.8 (V+); also elsewhere on the board
-2V5_CH: C104.2, C105.1, C108.1, C110.1, C111.1, C116.1, C173.1, U45.22 (AVSS), U45.28 (AVSS), U45.29 (AVSS), U45.30 (AVSS), U45.31 (AVSS), U45.32 (AVSS), U45.33 (AVSS), U45.34 (AVSS), U45.35 (AVSS), U45.36 (AVSS), U45.45 (AVSS), U45.51 (AVSS), U45.57 (AVSS); also elsewhere on the board
-5V_CH: C115.2, U29.2 (VSS), U44.4 (V-); also elsewhere on the board
/GP2.EXC+: R112.2, R165.2; also elsewhere on the board
/GP2.EXC-: R166.2, U29.1 (S1), U29.9 (S3); also elsewhere on the board
/fpga/ADC2.CLK: U45.16 (CLKIN); also elsewhere on the board
/fpga/ADC2.CS: U45.55 (~CS); also elsewhere on the board
/fpga/ADC2.DOUT: U45.6 (DOUT0); also elsewhere on the board
/fpga/ADC2.FSYNC: U45.15 (FSYNC); also elsewhere on the board
/fpga/ADC2.RESET: U45.52 (~RESET); also elsewhere on the board
/fpga/ADC2.SCLK: U45.56 (SCLK); also elsewhere on the board
/fpga/ADC2.SDI: U45.1 (SDI); also elsewhere on the board
/fpga/ADC2.SDO: U45.2 (SDO); also elsewhere on the board
/fpga/ADC2.START: U45.53 (START); also elsewhere on the board
/gp-ch2/converter/AINN0: C105.2, C107.1, R169.1, U45.44 (AINN0)
/gp-ch2/converter/AINP0: C104.1, C107.2, R168.1, U45.43 (AINP0)
/gp-ch2/converter/AINP1: R173.1, U45.41 (AINP1)
/gp-ch2/converter/AINP2: R174.1, R175.2, U45.39 (AINP2)
/gp-ch2/converter/AINP3: R167.1, R172.2, U45.37 (AINP3)
/gp-ch2/converter/CAL_EN: U29.7 (SEL3), U45.9 (DOUT3/GPIO3)
/gp-ch2/converter/CAPA: C116.2, U45.26 (CAPA), U45.27 (CAPA)
/gp-ch2/converter/CAPD: C117.2, U45.20 (CAPD)
/gp-ch2/converter/EXC_N: R170.2; also elsewhere on the board
/gp-ch2/converter/EXC_P: R167.2, U29.12 (S2); also elsewhere on the board
/gp-ch2/converter/LC_EN: R235.2, U29.6 (SEL4), U45.3 (GPIO0)
/gp-ch2/converter/LC_G: Q23.1, U29.5 (D4); also elsewhere on the board
/gp-ch2/converter/PRT_EN: U29.15 (SEL1), U45.4 (GPIO1)
/gp-ch2/converter/REFN: C106.1, C109.1, C173.2, R170.1, U45.47 (REFN), U45.48 (REFN)
/gp-ch2/converter/REFP: C106.2, C109.2, Q23.2, R111.1, U45.49 (REFP), U45.50 (REFP)
/gp-ch2/converter/S8_EN: U45.10 (GPIO4); also elsewhere on the board
/gp-ch2/converter/S9_EN: U45.11 (GPIO5); also elsewhere on the board
/gp-ch2/converter/SHLD_EN: R13.2, U45.12 (DIN1/GPIO6); also elsewhere on the board
/gp-ch2/converter/SIGN_BUF: R169.2; also elsewhere on the board
/gp-ch2/converter/SIGP_BUF: R168.2; also elsewhere on the board
/gp-ch2/converter/TX_EN: R237.2, U29.14 (SEL2), U45.8 (DOUT2/GPIO2); also elsewhere on the board
GND: C111.2, C112.1, C113.1, C114.1, C115.1, C117.1, R11.1, R13.1, R171.1, R172.1, R175.1, R235.1, R237.1, U29.3 (GND), U45.17 (DGND), U45.21 (DGND), U45.25 (AVDD2), U45.38 (AINN3), U45.40 (AINN2), U45.42 (AINN1); also elsewhere on the board
unnamed: Q23.3, R112.1
unnamed: R111.2, U29.13 (D2), U29.16 (D1)
unnamed 177: U29.8 (D3); also elsewhere on the board
unnamed: R165.1, R171.2, U44.3 (+)
unnamed: R173.2, U44.1, U44.2 (-)
unnamed: R166.1, U44.5 (+)
unnamed: R174.2, U44.6 (-), U44.7
unnamed: R11.2, U45.13 (DIN0/GPIO7)

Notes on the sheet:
REFERENCE SELECT
MONITOR
AVDD2
AVDD1
IOVDD
EXCITATION MONITOR
ANTI-ALIAS FILTER

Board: 2 copper layers, 301 parts (0 on the bottom side), 192 nets, no tracks yet.
